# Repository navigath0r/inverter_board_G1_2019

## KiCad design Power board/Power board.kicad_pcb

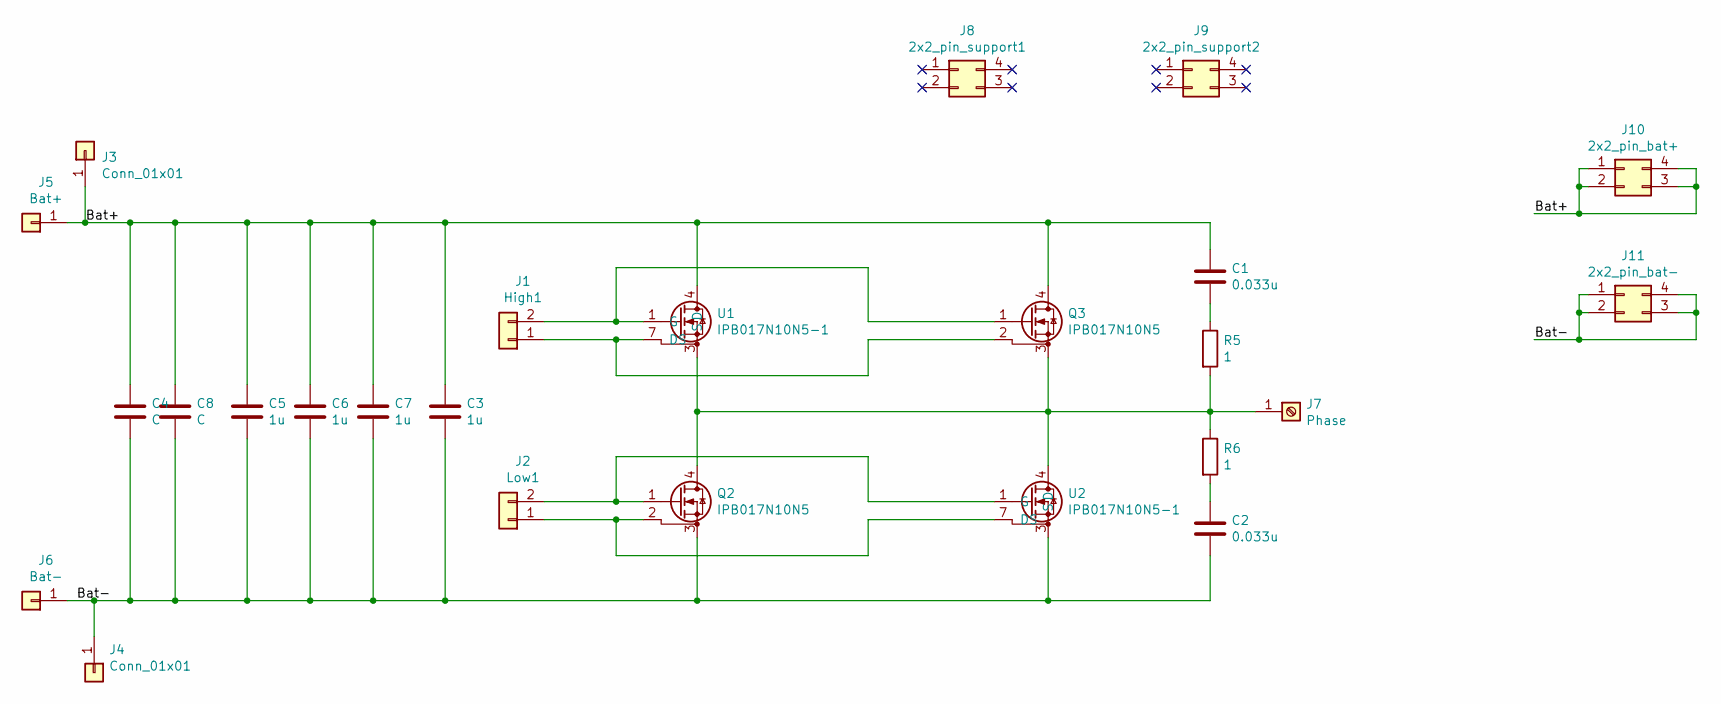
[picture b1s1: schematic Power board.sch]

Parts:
C1, C2: 0.033u; C_0805
C3, C6, C7: 1u; C_0805
C4: C; C_0805
C5: 1u; C_2220
C8: C; C_2220
J1: High1; Pin_Header_Straight_1x02_Pitch2.54mm_SMD_Pin1Left
J2: Low1; Pin_Header_Straight_1x02_Pitch2.54mm_SMD_Pin1Left
J3, J4: Conn_01x01; MountingHole_3.2mm_M3_DIN965_Pad
J5: Bat+; Busbar_connection
J6: Bat-; Busbar_connection
J7: Phase; Würth_PowerOne_SMD_M8
J8: 2x2_pin_support1; Pin_Header_Straight_2x02_Pitch2.54mm_SMD
J9: 2x2_pin_support2; Pin_Header_Straight_2x02_Pitch2.54mm_SMD
J10: 2x2_pin_bat+; Pin_Header_Straight_2x02_Pitch2.54mm_SMD
J11: 2x2_pin_bat-; Pin_Header_Straight_2x02_Pitch2.54mm_SMD
Q2, Q3: IPB017N10N5; TO-263-7_TabPin4
R5, R6: 1; R_0805
U1, U2: IPB017N10N5-1; TO-263-7_TabPin4

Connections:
/Bat+: C1.1, C3.1, C4.1, C5.1, C6.1, C7.1, C8.1, J3.1, J5.1, J10.1, J10.2, J10.3, J10.4, Q3.4 (D), U1.4 (D); also elsewhere on the board
/Bat-: C2.2, C3.2, C4.2, C5.2, C6.2, C7.2, C8.2, J4.1, J6.1, J11.1, J11.2, J11.3, J11.4, Q2.3 (S), Q2.5 (S), Q2.6 (S), Q2.7 (S), U2.2 (S), U2.3 (S), U2.5 (S), U2.6 (S); also elsewhere on the board
unnamed: C1.2, R5.1
unnamed: C2.1, R6.2
unnamed: J1.1, Q3.2 (DS), U1.7 (DS)
unnamed: J1.2, Q3.1 (G), U1.1 (G)
unnamed: J2.1, Q2.2 (DS), U2.7 (DS)
unnamed: J2.2, Q2.1 (G), U2.1 (G)
unnamed: J7.1, Q2.4 (D), Q3.3 (S), Q3.5 (S), Q3.6 (S), Q3.7 (S), R5.2, R6.1, U1.2 (S), U1.3 (S), U1.5 (S), U1.6 (S), U2.4 (D)

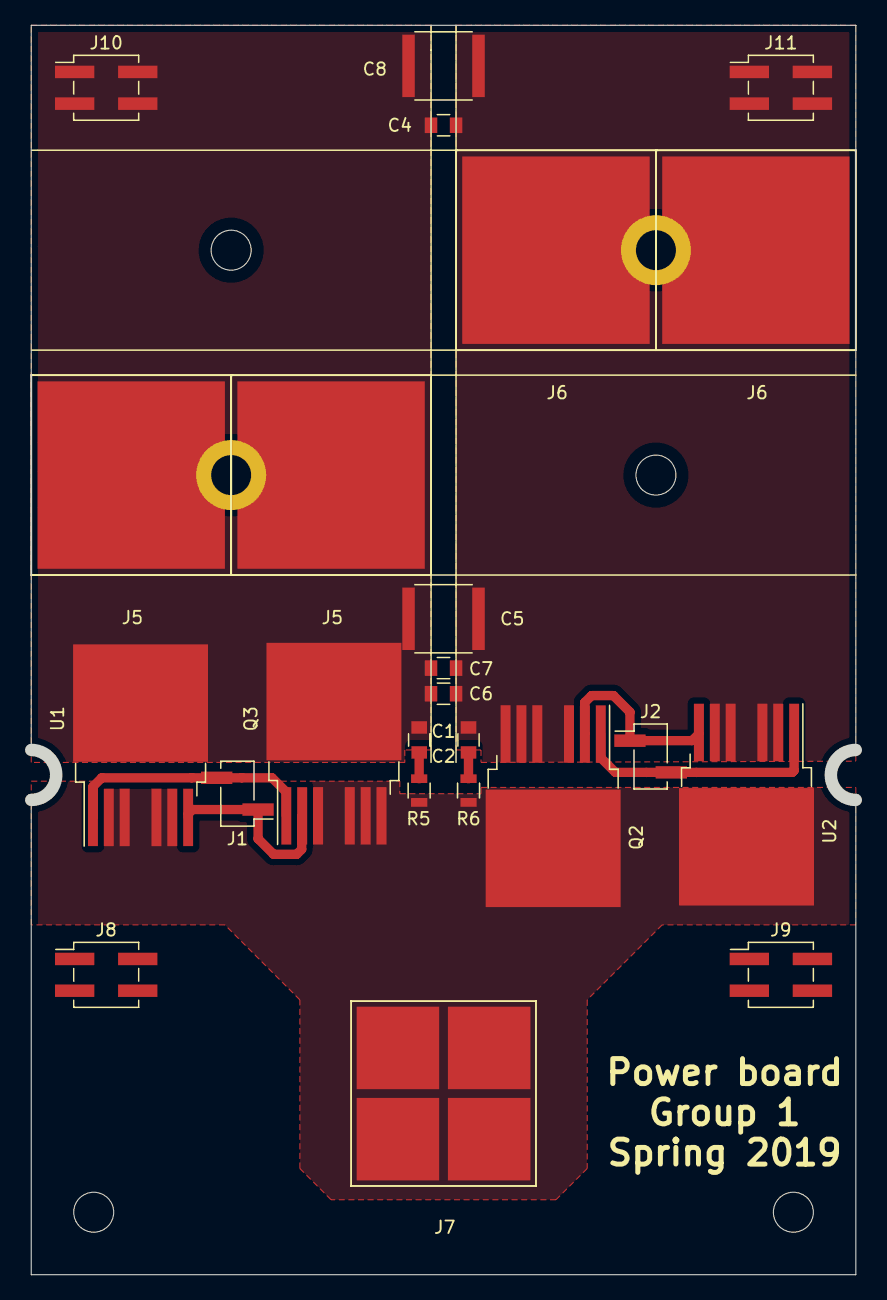
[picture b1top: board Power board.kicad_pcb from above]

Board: 2 copper layers, 66.0 x 99.1 mm, 26 parts (0 on the bottom side), 9 nets.

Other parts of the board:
J5#2: Bat+; Busbar_connection
J6#2: Bat-; Busbar_connection

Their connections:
/Bat+: J5#2.1; also elsewhere on the board
/Bat-: J6#2.1; also elsewhere on the board

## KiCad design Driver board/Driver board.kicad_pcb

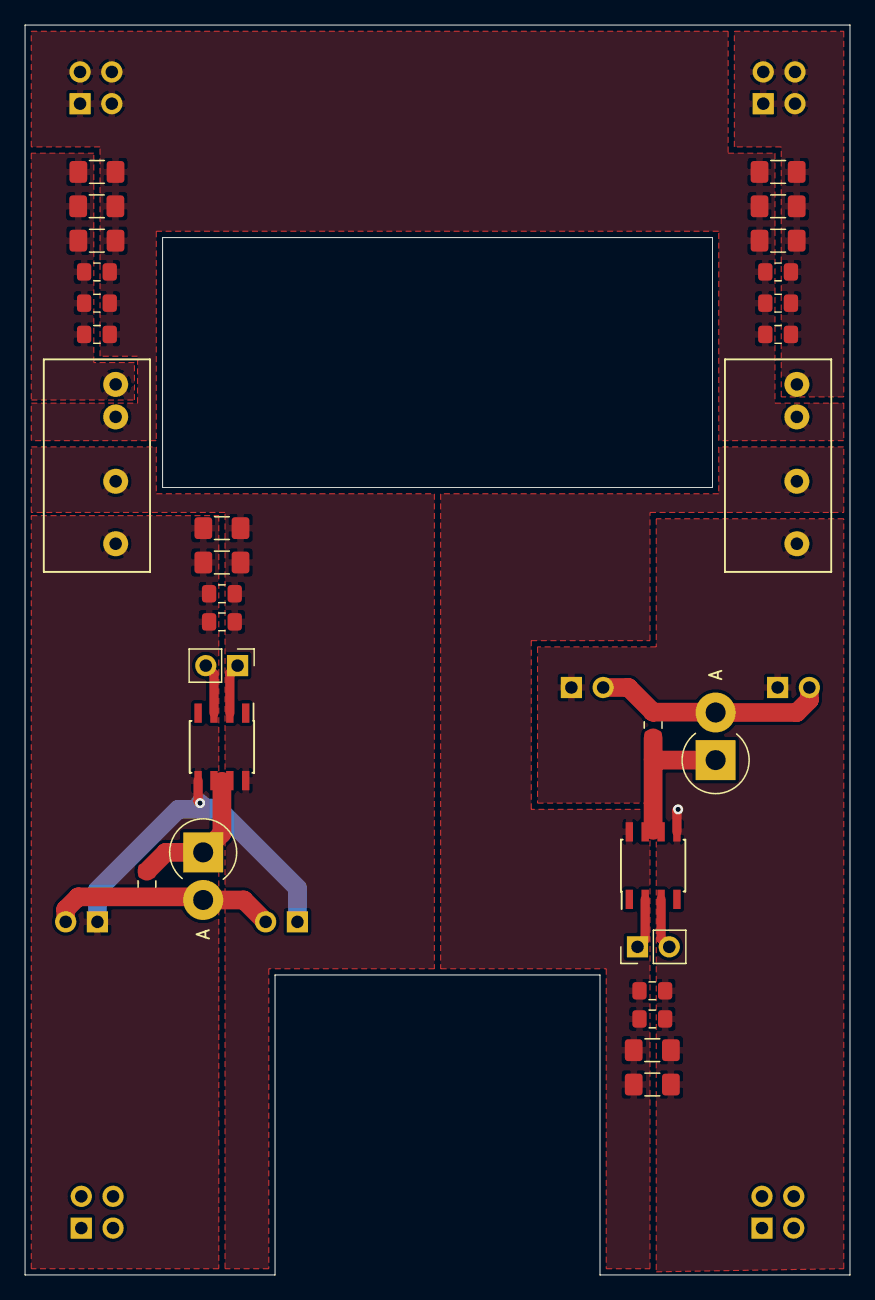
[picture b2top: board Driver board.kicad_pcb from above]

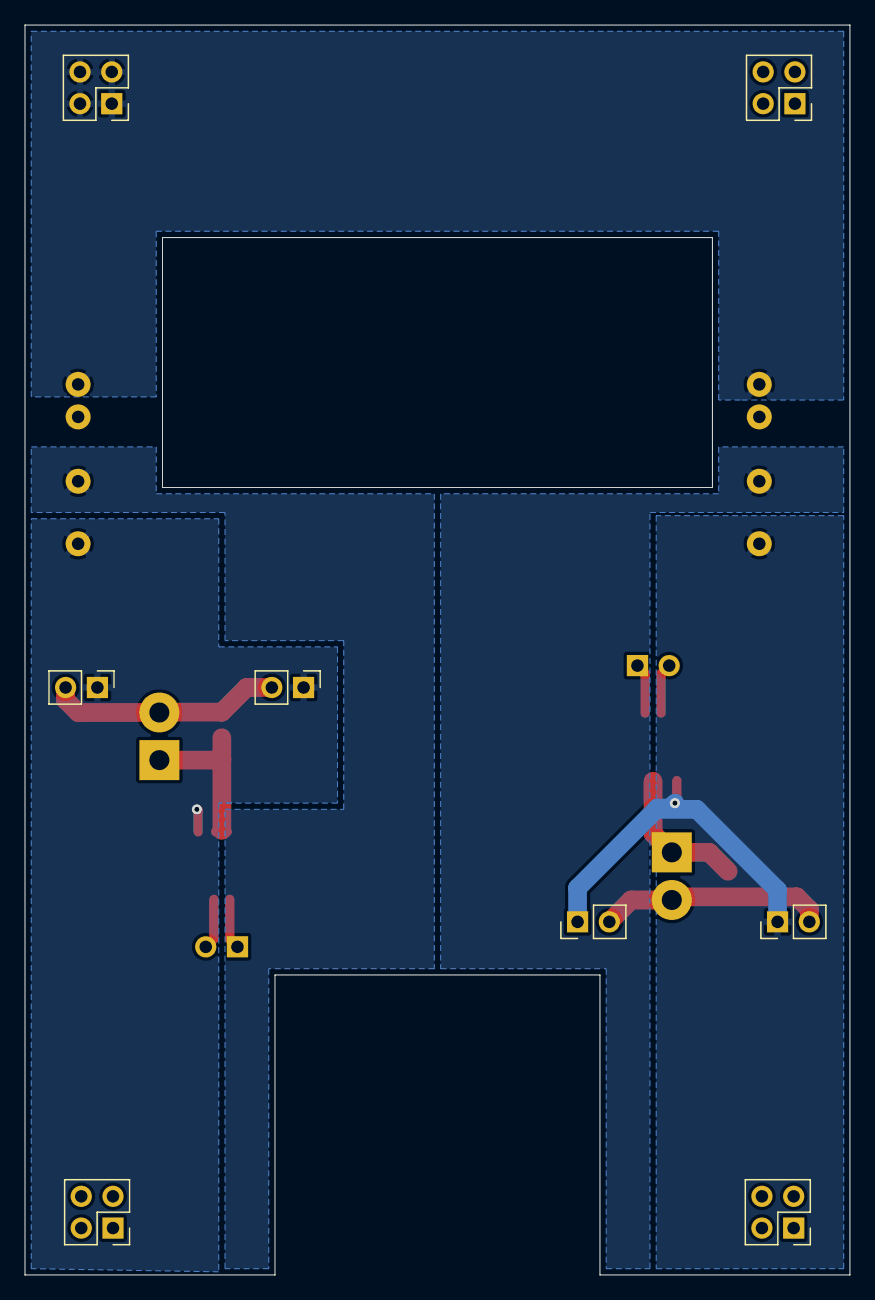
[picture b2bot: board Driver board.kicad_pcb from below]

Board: 2 copper layers, 66.0 x 100.0 mm, 38 parts (8 on the bottom side), 14 nets.

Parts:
C1, C8, C15, C22: 1n; C_1206_3216Metric_Pad1.42x1.75mm_HandSolder
C2, C9, C16, C23: 10n; C_0805_2012Metric_Pad1.15x1.40mm_HandSolder
C3, C10, C17, C24: 100n; C_1206_3216Metric_Pad1.42x1.75mm_HandSolder
C4, C11, C18, C25: 1u; C_0805_2012Metric_Pad1.15x1.40mm_HandSolder
C12, C26: 10n; C_1206_3216Metric_Pad1.42x1.75mm_HandSolder
C13, C27: 100n; C_0805_2012Metric_Pad1.15x1.40mm_HandSolder
D1, D2: D_Schottky; D_DO-201AD_P3.81mm_Vertical_AnodeUp
J1, J2, J7, J8: Conn_02x02_Odd_Even; PinHeader_2x02_P2.54mm_Vertical
J3, J5: Conn_01x02_Male; PinHeader_1x02_P2.54mm_Vertical
J4, J6, J9, J10: Conn_01x03_Male; PinHeader_1x02_P2.54mm_Vertical
R1, R2: R; R_0805_2012Metric_Pad1.15x1.40mm_HandSolder
U1, U3: MGS1R5
U2, U4: SI8261BAC-C-IS; SOIC-8_3.9x4.9mm_P1.27mm

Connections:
+BATT: C8.2, C9.2, C10.2, C11.2, C12.2, C13.2, C22.2, C23.2, C24.2, C25.2, C26.2, C27.2, J1.1, J1.2, J1.3, J1.4, U1.2, U3.2
-BATT: C8.1, C9.1, C10.1, C11.1, C12.1, C13.1, C22.1, C23.1, C24.1, C25.1, C26.1, C27.1, J2.1, J2.2, J2.3, J2.4, U1.1, U3.1
/VH+_isol: C1.2, C2.2, C3.2, C4.2, U1.3, U2.8
/VH-_isol: C1.1, C2.1, C3.1, C4.1, J4.1, J9.1, U1.4, U2.5
/VL+_isol: C15.2, C16.2, C17.2, C18.2, U3.3, U4.8
/VL-_isol: C15.1, C16.1, C17.1, C18.1, J6.1, J10.1, U3.4, U4.5
unnamed: D1.1, R1.1, U2.6, U2.7
unnamed: D1.2, J4.2, J9.2, R1.2
unnamed: D2.1, R2.1, U4.6, U4.7
unnamed: D2.2, J6.2, J10.2, R2.2
unnamed: J3.1, U2.2
unnamed: J3.2, U2.3
unnamed: J5.1, U4.2
unnamed: J5.2, U4.3

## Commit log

2019-04-17 Power and driver board is created
2019-04-18 MOSFET's added
2019-04-24 Gate resistors is added to power board
2019-04-25 schematic is done
2019-04-25 Power board is done
2019-04-26 Driver board basic schematic
2019-04-26 Driver board layout half-done
2019-04-26 Done PCB
2019-04-26 No real changes made
2019-04-27 Driver board wired, no decals yet
2019-04-28 No changes made
2019-04-28 No Chaniges made
2019-04-28 Added 3d models
2019-05-02 Updated With holes
2019-05-03 Final changes
2019-05-13 Gerber files made
